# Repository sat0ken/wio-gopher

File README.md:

# wio-gopher

Wio Terminal の背面 40pin ヘッダに挿す、Gopherくんデザインの基板です。
Gopher の目に WS2812B (フルカラー LED) を 2 個載せていて、TinyGo で光らせます。

## ファイル構成

| パス | 内容 |
|---|---|
| `wio-gopher.kicad_pro` / `.kicad_sch` / `.kicad_pcb` | KiCad プロジェクト |
| `lib/`, `lib.pretty/` | Wio Terminal 40pin ヘッダのシンボル / フットプリント |
| `wio-gopher/`, `wio-gopher.zip` | ガーバー・ドリルデータ |
| `firmware/` | TinyGo のファームウェア |

## 回路

| Wio Terminal 40pin | 接続先 |
|---|---|
| 1 (3V3) | D1, D2 VDD |
| 7 (PB14 / BCM4) | D1 DIN |
| GND | D1, D2 VSS |

D1 の DOUT は D2 の DIN につながっています。

## ファームウェア

パチンコ台風に、次の流れで光ります。

通常 (虹色) → リーチ (赤青の交互点滅が加速) → 抽選 → 大当たり (ストロボ連発) / ハズレ (赤がフェードアウト)

### 必要なもの

- [TinyGo](https://tinygo.org/)
- [tinygo.org/x/drivers](https://github.com/tinygo-org/drivers) (ws2812)

### 書き込み

Wio Terminal を USB で PC につないで、次を実行します。

```bash
cd firmware
tinygo flash -target=wioterminal .
```

### 注意

- 40pin ヘッダの 3V3 は、`OUTPUT_CTR_3V3` (PC15) を Low にしないと出力されません。TinyGo は起動時にこれを設定しないので、ファームウェアの中で有効にしています。
- WS2812B の電源電圧の仕様は 3.5V 以上なので、3.3V での給電は仕様外です。表示が乱れる場合は `firmware/main.go` の `brightness` を下げてください。

## ライセンス

[MIT](LICENSE)

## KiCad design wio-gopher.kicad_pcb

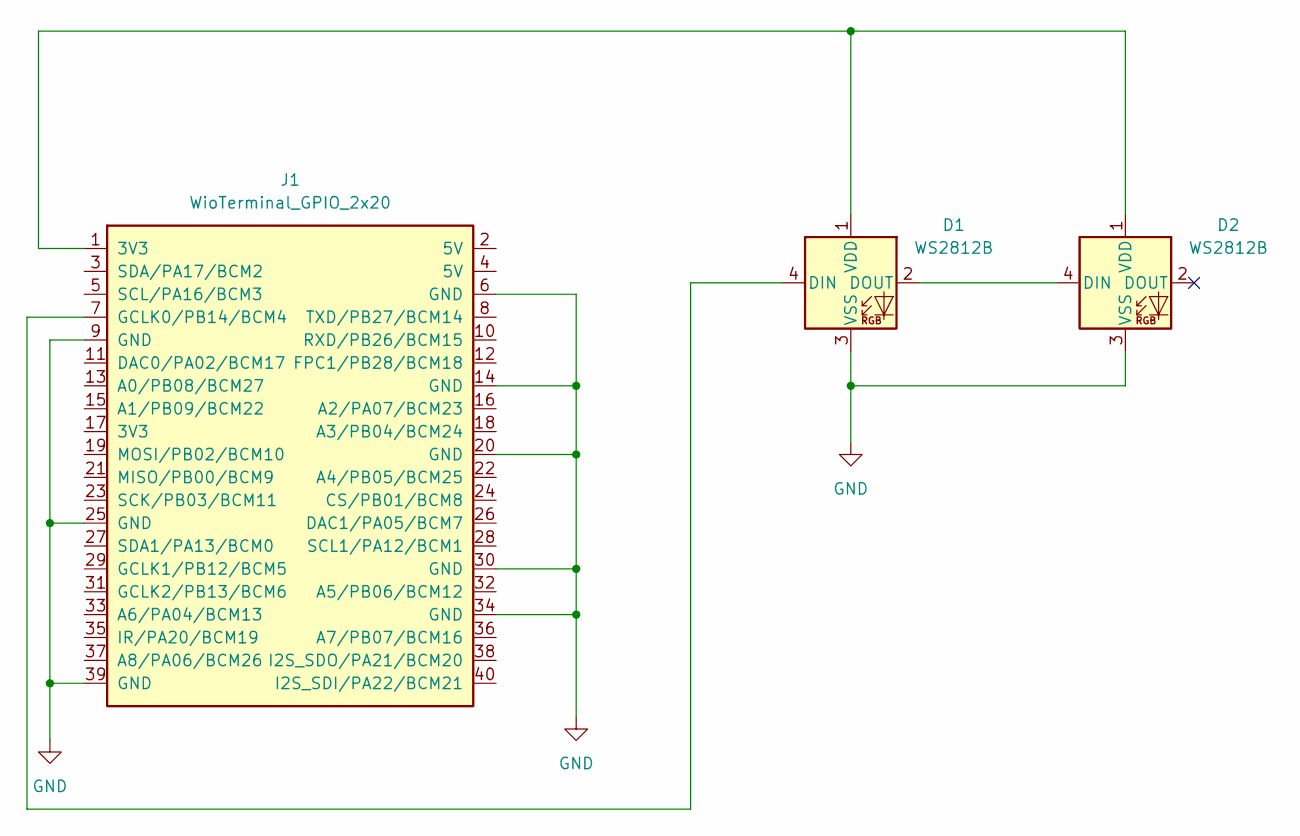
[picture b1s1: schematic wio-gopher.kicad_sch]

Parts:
D1, D2: WS2812B; LED_WS2812B_PLCC4_5.0x5.0mm_P3.2mm
J1: WioTerminal_GPIO_2x20; WioTerminal_Carrier_PinHeader_2x20

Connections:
GND: D1.3 (VSS), D2.3 (VSS), J1.6 (GND), J1.9 (GND), J1.14 (GND), J1.20 (GND), J1.25 (GND), J1.30 (GND), J1.34 (GND), J1.39 (GND)
unnamed: D1.4 (DIN), J1.7 (GCLK0/PB14/BCM4)
unnamed: D1.2 (DOUT), D2.4 (DIN)
unnamed: D1.1 (VDD), D2.1 (VDD), J1.1 (3V3)

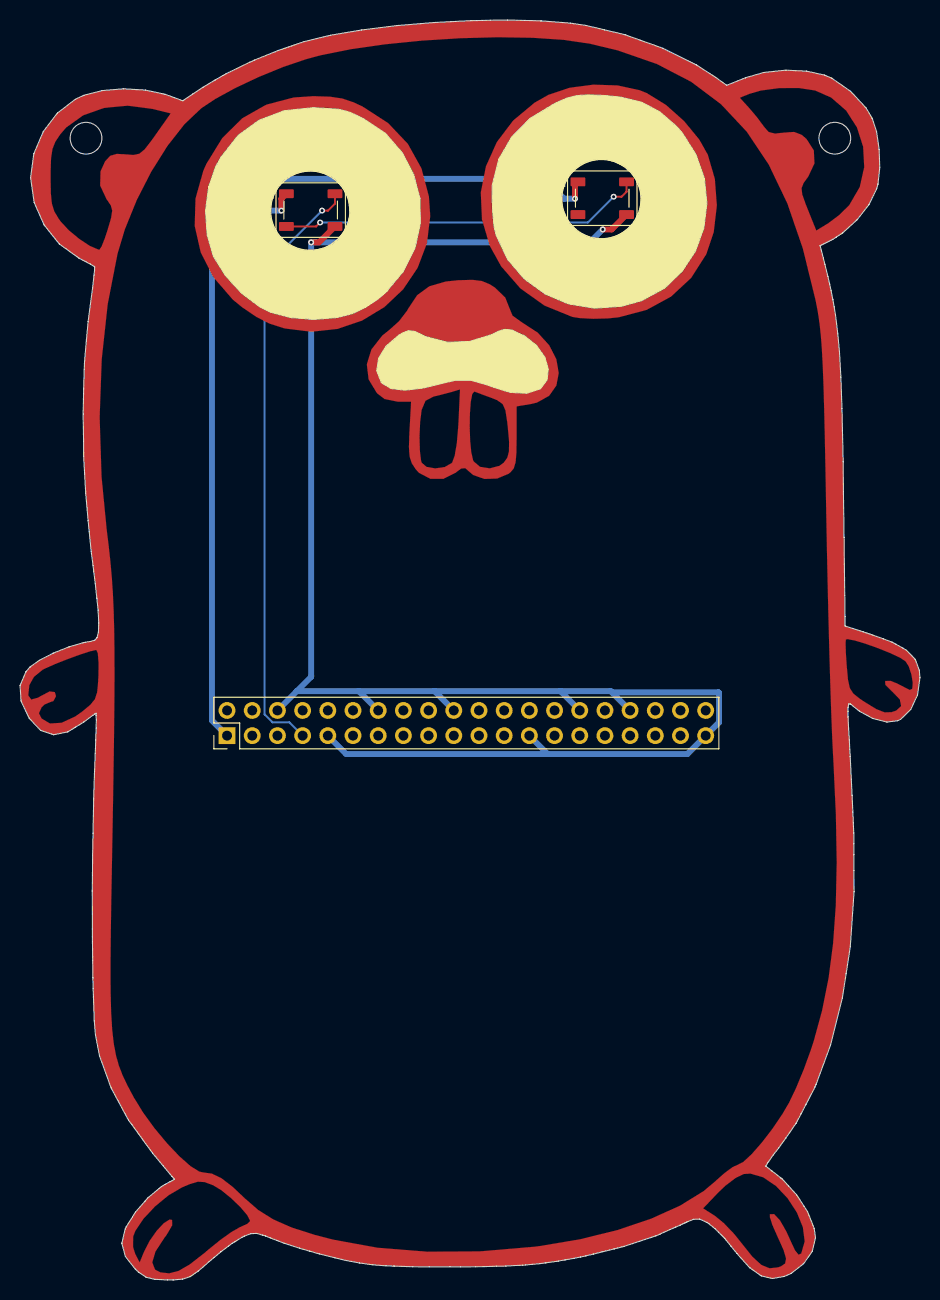
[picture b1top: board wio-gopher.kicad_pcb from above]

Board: 2 copper layers, 90.7 x 127.0 mm, 3 parts (0 on the bottom side), 4 nets.
